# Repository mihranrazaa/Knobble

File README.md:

# Knobble
A modern design for not so common radios.

---

# Overview

Knobble is a Rasberry pi based portable Radio scanning system design for real time monitoring and interacting with different radio frequncies via an RTL-SDR dongle. It can help you to listen through FM, aviation, emergency, amateur, and public service frequencies.

---

## Features

- Runs on Rasberry PI zero 2 W.
- Multi-band scanning across FM, aviation, emergency, amateur, and police frequencies
- Preset system with multiple frequency banks and persistent storage.
- Automatic and manual scan modes
- Better shutdown process
- Oled Display for sharing all the relevant live info.
- and a cool CAD Design for emotional support lol.

---

## Controls

| Control                   | Action                                         |
| ------------------------- | ---------------------------------------------- |
| **Rotate Encoder**        | Adjust volume or frequency                     |
| **Encoder Button (tap)**  | Start/stop scanning                            |
| **Encoder Button (hold)** | Toggle mute/unmute                             |
| **Switch 1**              | Cycle through preset banks                     |
| **Switch 2**              | Toggle scan mode (Manual / Auto / Preset)      |
| **Switch 3**              | Change radio service type (FM, Aviation, etc.) |

---

## Files to build 

### PCB 

The files for the PCB and Schematics are available in the PCB folder and gerber files are added in the Production folder..

### 3D Case (CAD)

The step files for the keyboard are available in the CAD folder and also in the Production Folder.

**BASE**

**TOP**

---

## Combined Images

Can't add a combine image of pcb with components my laptop can't handle all that together..
Other than this you just have to purchase the Components given in the BOM and solder and assemble them.

---

## BOM 

| Component             | Quantity | Note                                                | Price      | Link                                                                                                                                                                                                                                                                                                                                                                                                                                                                                                                                  |
| --------------------- | -------- | --------------------------------------------------- | ---------- | ------------------------------------------------------------------------------------------------------------------------------------------------------------------------------------------------------------------------------------------------------------------------------------------------------------------------------------------------------------------------------------------------------------------------------------------------------------------------------------------------------------------------------------- |
| Rasberry pi zero 2 w  | 1        | Controlling UNIT                                    | 16USD      | [Available](https://amzn.in/d/c275gW4)                                                                                                                                                                                                                                                                                                                                                                                                                                                                                                |
| RTL-SDR               | 1        | most important for the project..                    | 51USD     | [Available](https://www.fabtolab.com/rtl-sdr-blog-v4-r828d-rtl2832u-1ppm-tcxo-sma-software-defined-radio-dipole-antenna-kit?search=RTL-SDR%20Blog)                           |
| 1.3 inch oled display | 1        | It has 2 extra Stabilizers just in case..           | 12USD       | [Available](https://www.amazon.in/OLED-Display-display-module-Blue/dp/B094W7TDKG/ref=sr_1_2?crid=3Q8FJIB11QGHE&dib=eyJ2IjoiMSJ9.B7UJuX2tN4RE5qUC46uLygug8WxLWjSOgkyJMu7-EXH34VlmGjoBuWPJP22TIlHrdvHc4LjgYXnp2hc3py_BE1EeIB7uhaHjrsFRpNXUNRdJJqR5dObtouw747pxiRkK7KSuLolsob9jHVAnGcaUQn5teiI1JISdhIaT3GLy4wLR4472yi4Cjp-WcG2tbnTWI6ai3V6rmwGP0F4cLP8XCu0CnJj878OKKMi18kqWd-w.z5miULqVkwuwROpuzjmyTGVz6pdf8Er0rOkTBH4zD-s&dib_tag=se&keywords=1%2C3+inch+oled+display&qid=1750676109&sprefix=1%2C3+inch+oled+displa%2Caps%2C227&sr=8-2) |
| macro switches        | 3        | user input they are 50 pcs the link i have provided | 0.9USD     | [Available](https://amzn.in/d/1zYgQJ0)                                                                                                                                                                                                                                                                                                                                                                                                                                                                                                |
| Rotary encoder        | 1        | User input                                          | 0.9USD     | [Available](https://amzn.in/d/8Zozbdr)                                                                                                                                                                                                                                                                                                                                                                                                                                                                                                |
| PCM5102A DAC          | 1        | For connecting external speaker, headphones, etc    | 26USD      | [Available](https://amzn.in/d/7MQeXHS)                                                                                                                                                                                                                                                                                                                                                                                                                                                                                                |
| UPS Hat               | 1        | For portability                                     | 26USD      | [Available](https://hubtronics.in/ups-hat-c)                                                                                                                                                                                                                                                                                                                                                                                                                                                                                          |
| PCB                   | **       | JLCPCB ftw                                          | -          |                                                                                                                                                                                                                                                                                                                                                                                                                                                                                                                                       |
| CAD                   | **       | Legion ftw                                          | -          |                                                                                                                                                                                                                                                                                                                                                                                                                                                                                                                                       |
| Total                 |          |                                                     | 135-145USD |                                                                                                                                                                                                                                                                                                                                                                                                                                                                                                                                       |

**I know it going above 150USD so i'm ready to pay the remaining cost...**

---

## Next Update 

- I want to add offline music listening...

---

## Extra Stuff

### Gratitude
- Thanks to Hackclub and Hackpad for making me do this brilliant project, More coming :).
- Thanks to my potato for helping me till the end.
- Thanks to myself for completing the project and not getting distracted with another project.
- And Thank you for Reading?

### Inspiration
**Going to Undercity!!** and i always wanted to build thiss project becuase RF always makes me curious it is like another invisible world which we can only access through speacial gears feels Magical...

### Challanging
Building the custom case.. i don't have the words to express my pain...

---

## End
Check my [BLOG](https://mihranrazaa.pages.dev/)
~ mihranrazaa(If you are reading this please review HappyUSB too ToT )

BYEEE

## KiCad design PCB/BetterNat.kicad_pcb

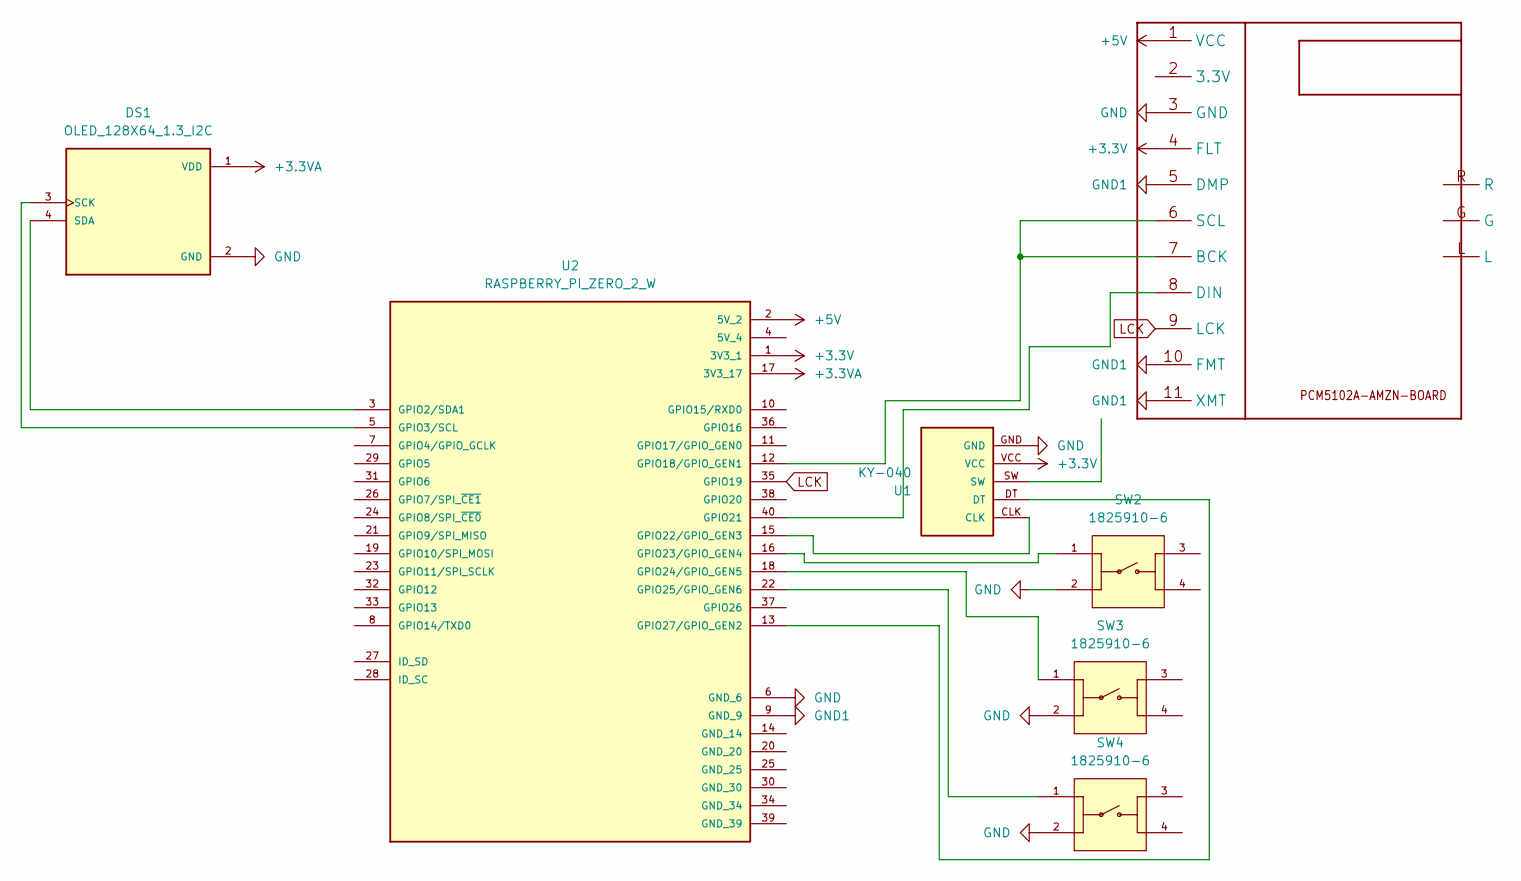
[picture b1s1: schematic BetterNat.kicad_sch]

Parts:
1: PCM5102A-AMZN-BOARD
DS1: OLED_128X64_1.3_I2C; LCD_OLED_128X64_1.3_I2C3D; PARTREV NA
SW2, SW3, SW4: 1825910-6; SW_1825910-6-43D; PARTREV C10
U1: KY-040; KY-040-PORT3D
U2: RASPBERRY_PI_ZERO_2_W; MODULE_RASPBERRY_PI_ZERO_2_W3d; PARTREV April 2024

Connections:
+3.3V: 1.4 (FLT), U1.VCC, U2.1 (3V3_1)
+3.3VA: DS1.1 (VDD), U2.17 (3V3_17)
+5V: 1.1 (VCC), U2.2 (5V_2)
GND: 1.3 (GND), DS1.2 (GND), SW2.2, SW3.2, SW4.2, U1.GND, U2.6 (GND_6)
GND1: 1.5 (DMP), 1.10 (FMT), 1.11 (XMT), U2.9 (GND_9)
LCK: 1.9 (LCK), U2.35 (GPIO19)
unnamed: 1.6 (SCL), 1.7 (BCK), U2.12 (GPIO18/GPIO_GEN1)
unnamed: 1.8 (DIN), U2.40 (GPIO21)
unnamed: DS1.3 (SCK), U2.5 (GPIO3/SCL)
unnamed: DS1.4 (SDA), U2.3 (GPIO2/SDA1)
unnamed: U1.CLK, U2.15 (GPIO22/GPIO_GEN3)
unnamed: SW2.1, U2.16 (GPIO23/GPIO_GEN4)
unnamed: SW3.1, U2.18 (GPIO24/GPIO_GEN5)
unnamed: SW4.1, U2.22 (GPIO25/GPIO_GEN6)
unnamed: U1.DT, U2.13 (GPIO27/GPIO_GEN2)

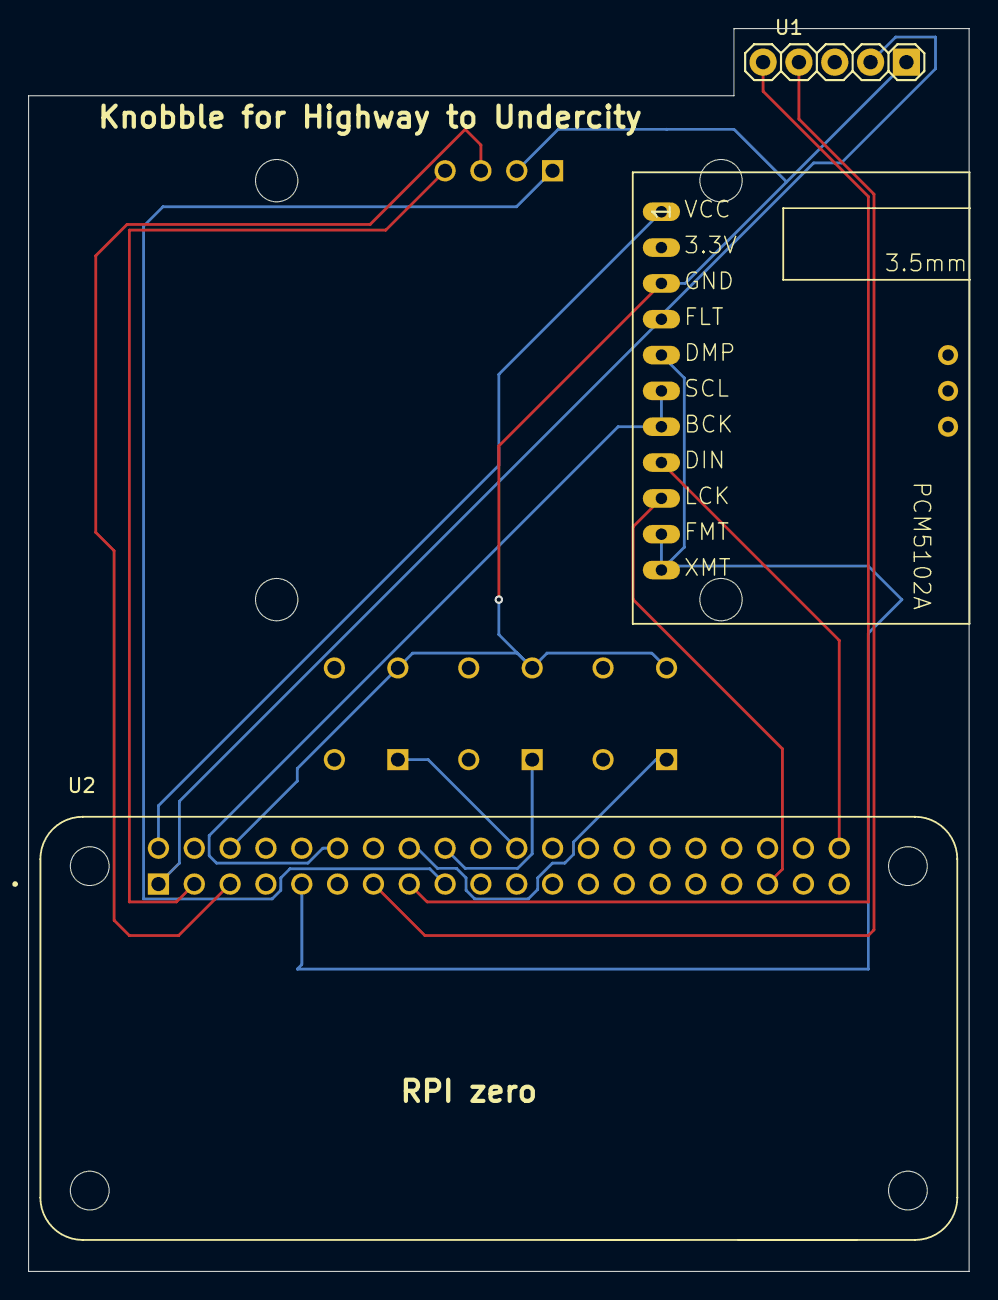
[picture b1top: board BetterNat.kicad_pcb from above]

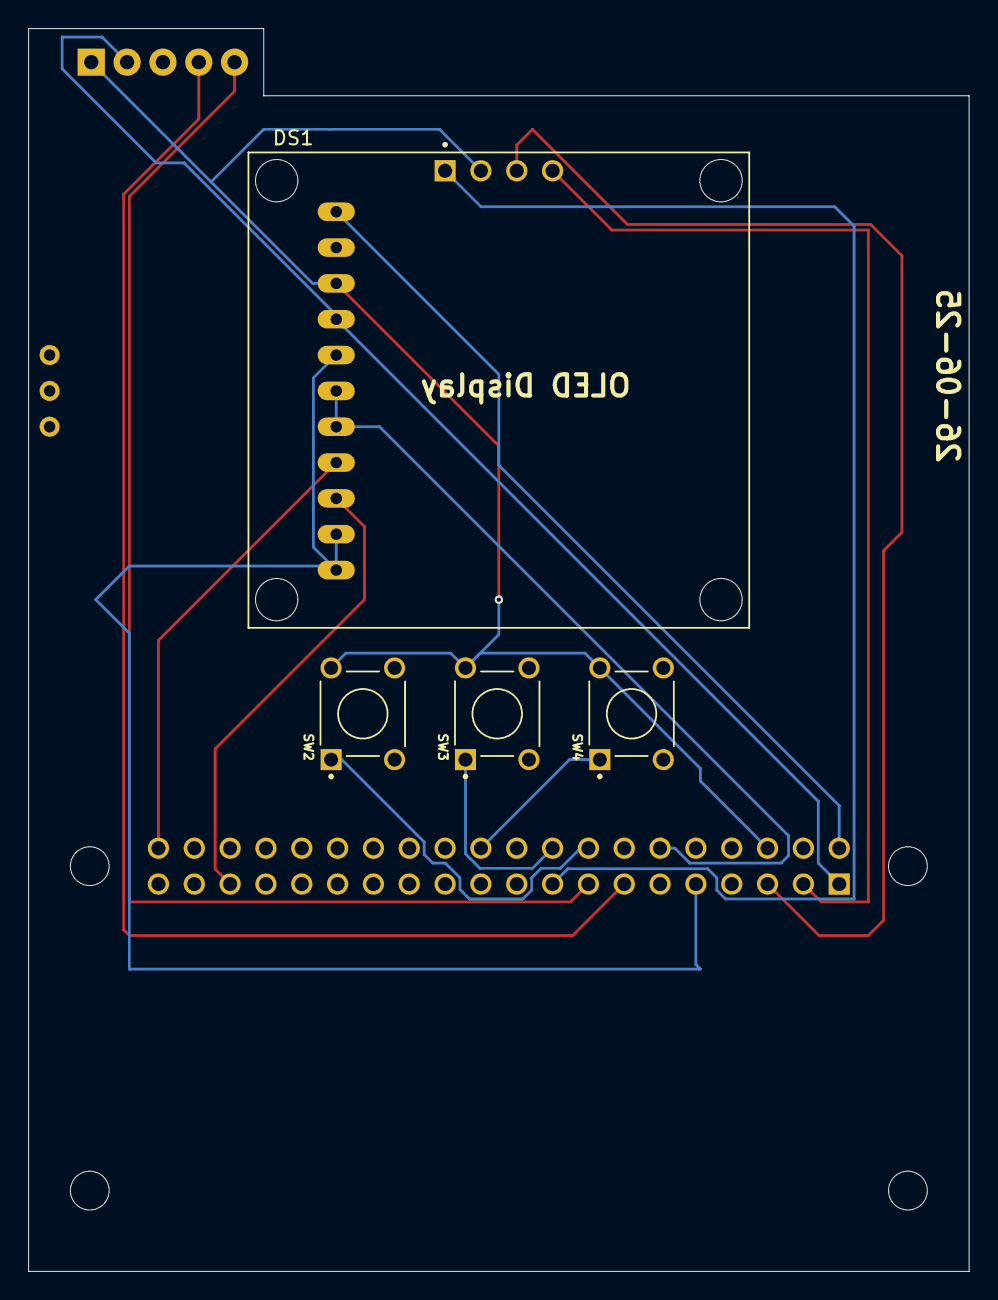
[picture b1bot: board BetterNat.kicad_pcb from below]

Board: 2 copper layers, 66.7 x 88.1 mm, 7 parts (4 on the bottom side), 15 nets.

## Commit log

2025-06-17 update Journal
2025-06-23 update Jou*
2025-06-23 update journal and readm*
2025-06-23 release V1
2025-06-29 update V2
2025-06-30 Update timing and header in journal
2025-07-02 removed ai cover
2025-07-12 update software
2025-07-15 test new code
2025-07-15 added uninstall script
